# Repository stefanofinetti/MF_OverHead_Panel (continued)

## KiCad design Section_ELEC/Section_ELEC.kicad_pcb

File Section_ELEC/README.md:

# ELEC section board (v2)

The v2 board under the ELEC panel. It carries the panel's switches, annunciator LEDs and backlight, at their v1 positions, and reaches the mainboard through one ribbon and one pair of backlight wires. There are no ICs on it. The design rules shared by the eight section boards are in [`docs/board-split.md`](../docs/board-split.md).

* **PCB:** 177.5 × 39.5 mm, 2 layers, 1.6 mm. Every v1 hole is kept.
* **Status:** routed with Freerouting. ERC, DRC and schematic parity are clean. Not yet ordered.

**Top**, the panel side:

**Bottom**, with the connectors:

Rendered by KiCad from the board file. The bottom is seen from below, so it is mirrored against the top.

## Connectors

Both are new on v2 and sit on the **back**, so nothing new stands proud of the front.

| Ref | What | Goes to |
|---|---|---|
| J1 | Shrouded IDC header, 20 pins, SMD | J703 on the mainboard, straight ribbon, pin 1 to pin 1 |
| J2 | JST PH, 2 pins, SMD. Pin 1 `+9V_BL` (`+`), pin 2 the switched return (`−`) | screw terminal J603 on the mainboard |

J1 and J2 are on the back, top edge, left end.

The signal on every ribbon pin is in the design document: [ELEC — 20 pins](../docs/board-split.md#elec--20-pins).

## Switches

| Ref | Switch | Type | v1 ref |
|---|---|---|---|
| SW1 | ELEC OXY CREW SUPPLY | Korry | SW14 |
| SW2 | ELEC BATT 1 | Korry | SW15 |
| SW3 | ELEC BATT 2 | Korry | SW16 |

## Annunciators

Anodes on `+5V_LED` from the ribbon, cathodes back down the ribbon to their TLC5927 output. No resistors: the TLC5927 sets the current.

| Ref | Colour | Legend | Chain bit | Driver | v1 ref |
|---|---|---|---|---|---|
| D1 | white | `OXY_CREW_SUPPLY_OFF` | `ANN_LOWER` 4 | U501 (v1 U6) | D103 |
| D2 | amber | `ELEC_BATT_1_FAULT` | `ANN_UPPER` 14 | U503 (v1 U8) | D1 |
| D3 | white | `ELEC_BATT_1_OFF` | `ANN_LOWER` 15 | U501 (v1 U6) | D106 |
| D4 | amber | `ELEC_BATT_2_FAULT` | `ANN_UPPER` 13 | U503 (v1 U8) | D3 |
| D5 | white | `ELEC_BATT_2_OFF` | `ANN_LOWER` 14 | U501 (v1 U6) | D107 |

## Backlight

10 LEDs, 1206 (D6–D15), on 9 V, in 5 strings of two with 150 Ω (R1–R5). Each string runs at about 17 mA. `K` marks every cathode on the silkscreen.

## Assembly notes

* J3 is the BATT 1 OLED socket (PCA9548A channel 0) and J4 the BATT 2 one (channel 1), where they were on v1: 1 GND, 2 +3V3, 3 SCL, 4 SDA.
* R5 is new, 150 Ω on the back. It replaces v1 R57, which sat across the seam on the AIR COND side.
* Every part has its value, polarity or pin 1 on the silkscreen of its own side. Each part's description in the schematic names its v1 reference.

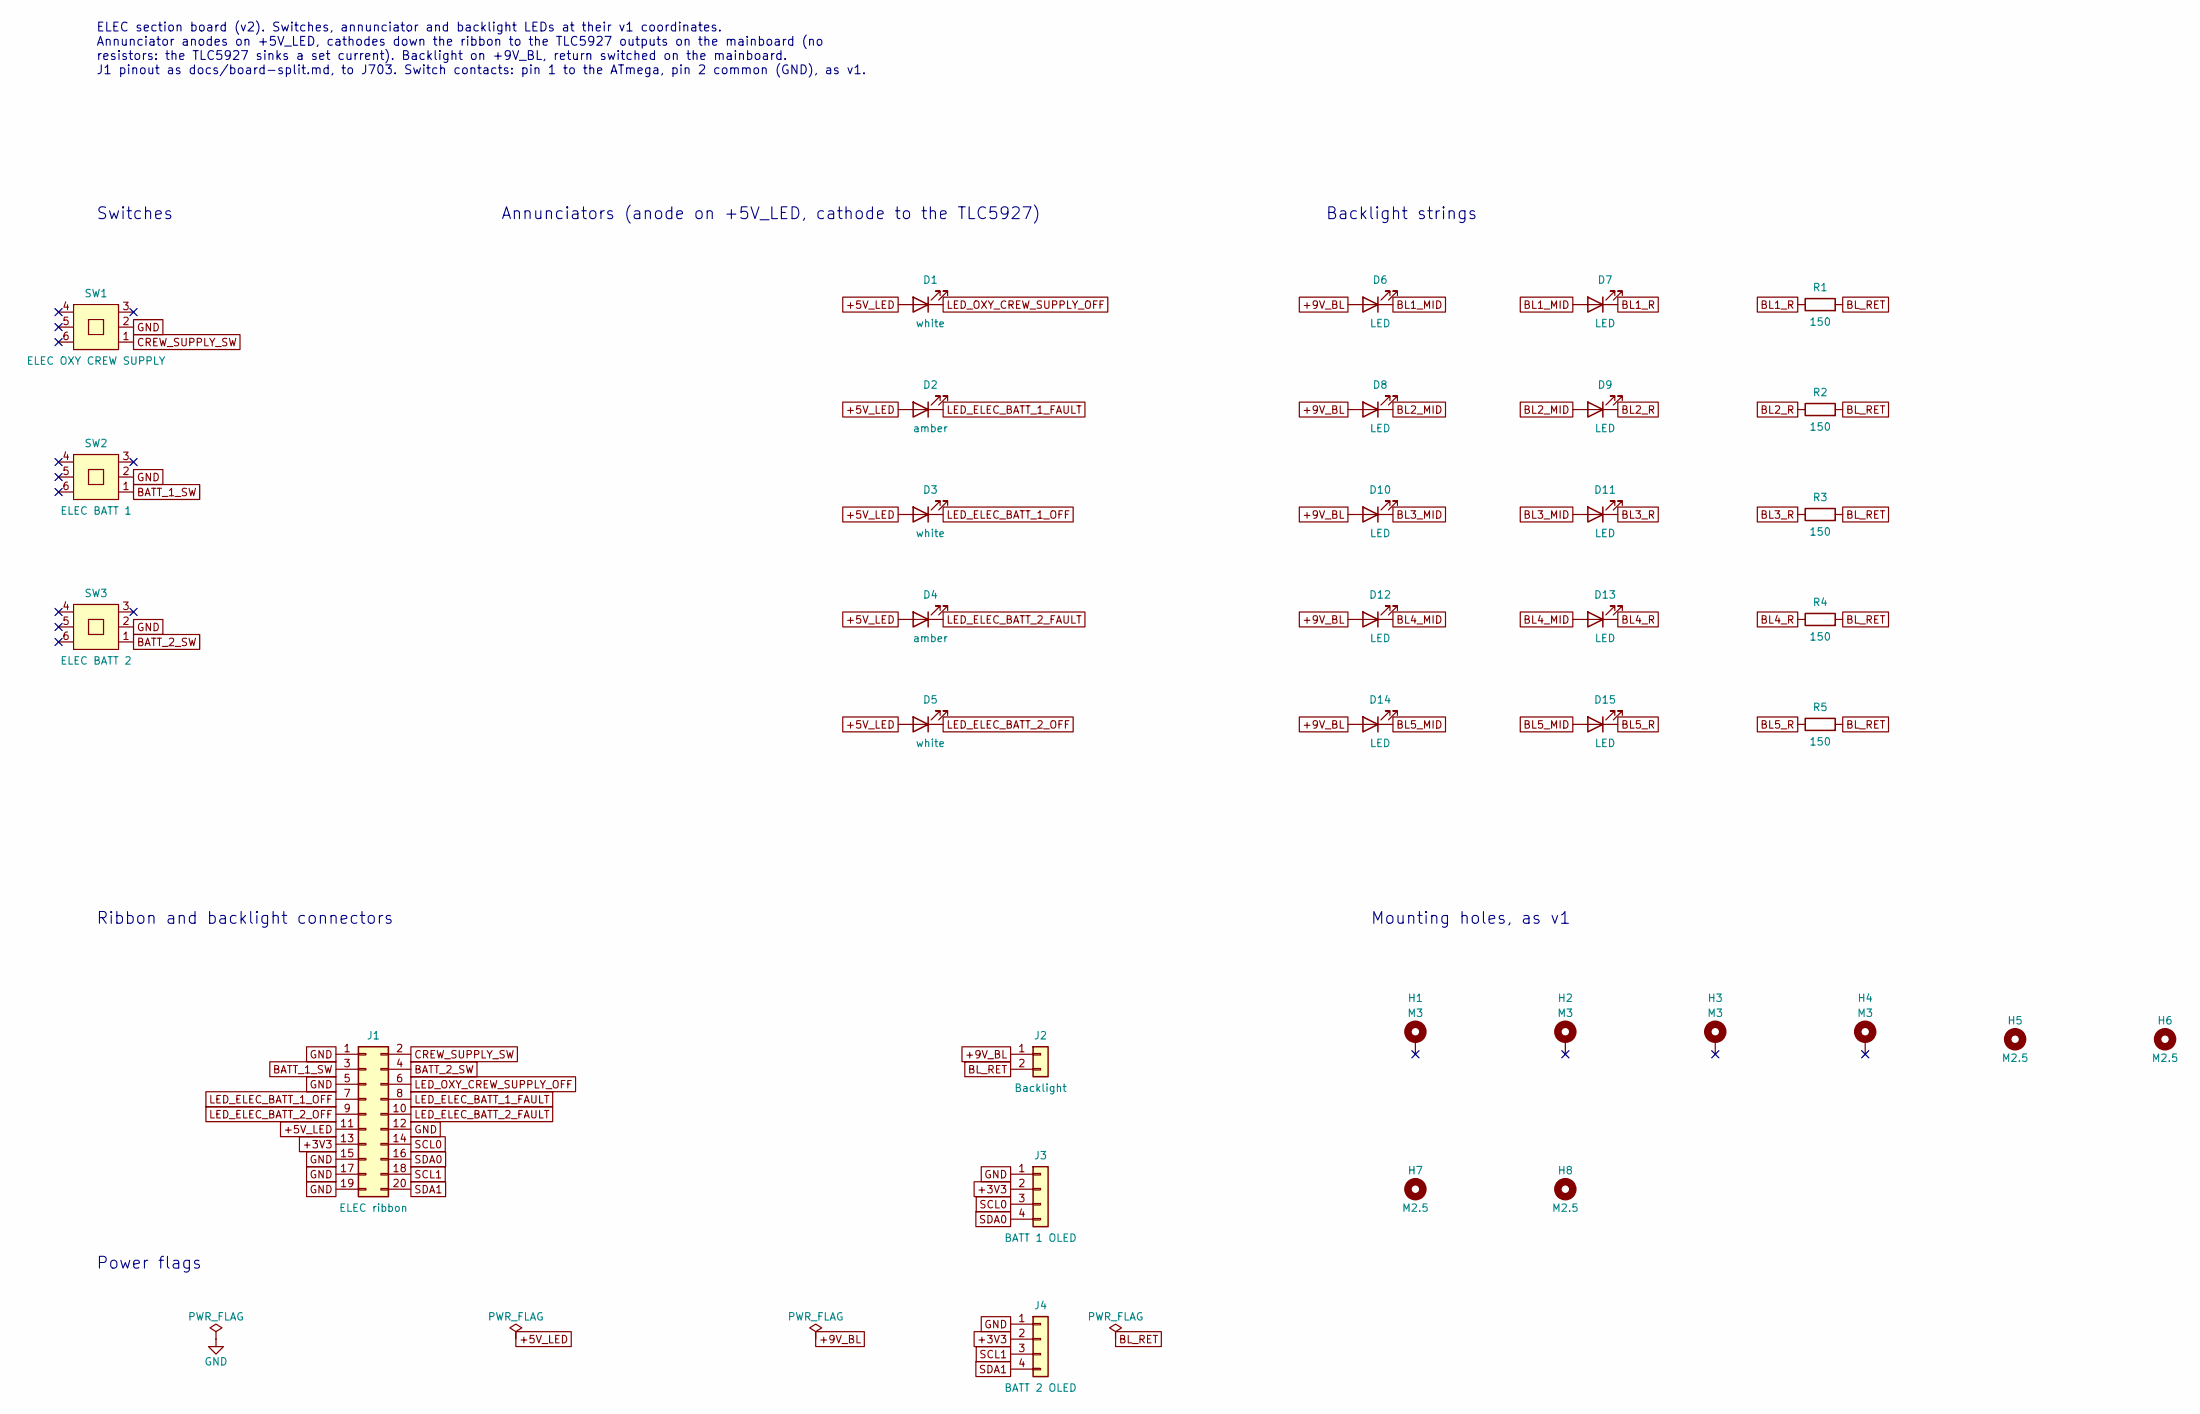
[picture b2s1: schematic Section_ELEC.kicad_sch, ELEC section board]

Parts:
D1, D3, D5: white; LED_Rectangular_W3.9mm_H1.8mm_FlatTop
D2, D4: amber; LED_Rectangular_W3.9mm_H1.8mm_FlatTop
D6, D7, D8, D9, D10, D11, D12, D13, D14, D15: LED; LED_1206_3216Metric_Pad1.42x1.75mm_HandSolder
H1, H2, H3, H4: M3; MountingHole_3.2mm_M3_DIN965_Pad_TopBottom
H5, H6, H7, H8: M2.5; MountingHole_2.7mm_M2.5
J1: ELEC ribbon; IDC-Header_2x10_P2.54mm_Vertical_SMD
J2: Backlight; JST_PH_B2B-PH-SM4-TB_1x02-1MP_P2.00mm_Vertical
J3: BATT 1 OLED; PinSocket_1x04_P2.54mm_Vertical
J4: BATT 2 OLED; PinSocket_1x04_P2.54mm_Vertical
R1, R2, R3, R4, R5: 150; R_1206_3216Metric_Pad1.30x1.75mm_HandSolder
SW1: ELEC OXY CREW SUPPLY; G-Switch_PS-7054DVB-6PN
SW2: ELEC BATT 1; G-Switch_PS-7054DVB-6PN
SW3: ELEC BATT 2; G-Switch_PS-7054DVB-6PN

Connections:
+3V3: J1.13, J3.2, J4.2
+5V_LED: D1.2 (A), D2.2 (A), D3.2 (A), D4.2 (A), D5.2 (A), J1.11
+9V_BL: D6.2 (A), D8.2 (A), D10.2 (A), D12.2 (A), D14.2 (A), J2.1
BATT_1_SW: J1.3, SW2.1
BATT_2_SW: J1.4, SW3.1
BL1_MID: D6.1 (K), D7.2 (A)
BL1_R: D7.1 (K), R1.1
BL2_MID: D8.1 (K), D9.2 (A)
BL2_R: D9.1 (K), R2.1
BL3_MID: D10.1 (K), D11.2 (A)
BL3_R: D11.1 (K), R3.1
BL4_MID: D12.1 (K), D13.2 (A)
BL4_R: D13.1 (K), R4.1
BL5_MID: D14.1 (K), D15.2 (A)
BL5_R: D15.1 (K), R5.1
BL_RET: J2.2, R1.2, R2.2, R3.2, R4.2, R5.2
CREW_SUPPLY_SW: J1.2, SW1.1
GND: J1.1, J1.5, J1.12, J1.15, J1.17, J1.19, J3.1, J4.1, SW1.2, SW2.2, SW3.2
LED_ELEC_BATT_1_FAULT: D2.1 (K), J1.8
LED_ELEC_BATT_1_OFF: D3.1 (K), J1.7
LED_ELEC_BATT_2_FAULT: D4.1 (K), J1.10
LED_ELEC_BATT_2_OFF: D5.1 (K), J1.9
LED_OXY_CREW_SUPPLY_OFF: D1.1 (K), J1.6
SCL0: J1.14, J3.3
SCL1: J1.18, J4.3
SDA0: J1.16, J3.4
SDA1: J1.20, J4.4

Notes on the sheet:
Backlight strings
Power flags
Ribbon and backlight connectors
Switches
Mounting holes, as v1
ELEC section board (v2). Switches, annunciator and backlight LEDs at their v1 coordinates. Annunciator anodes on +5V_LED, cathodes down the ribbon to the TLC5927 outputs on the mainboard (no resistors: the TLC5927 sinks a set current). Backlight on +9V_BL, return switched on the mainboard. J1 pinou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
Annunciators (anode on +5V_LED, cathode to the TLC5927)

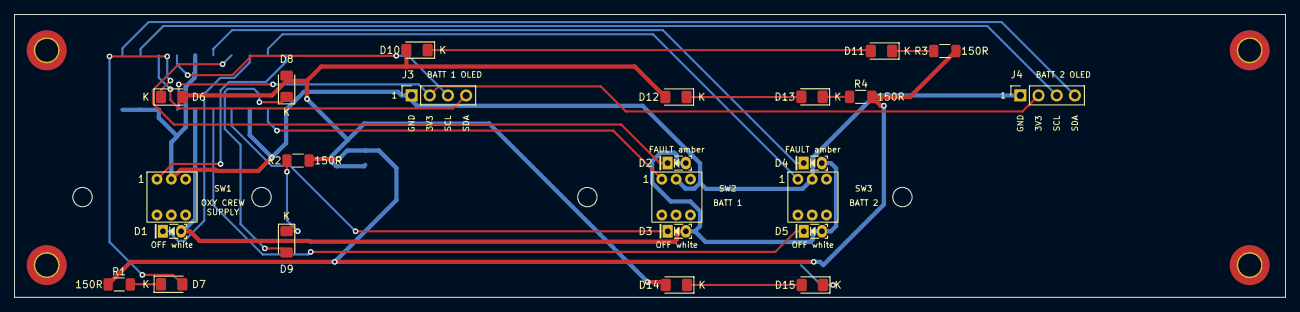
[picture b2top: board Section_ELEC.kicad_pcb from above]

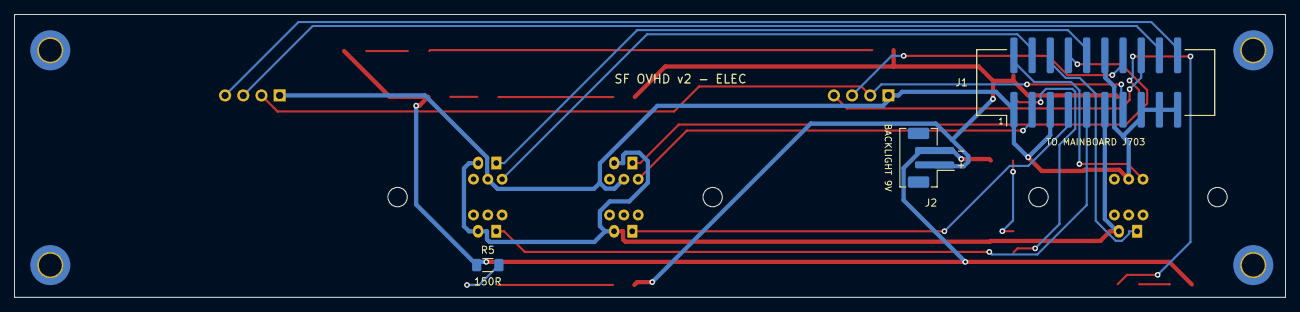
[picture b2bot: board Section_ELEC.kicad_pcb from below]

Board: 2 copper layers, 177.5 x 39.5 mm, 35 parts (3 on the bottom side), 27 nets.

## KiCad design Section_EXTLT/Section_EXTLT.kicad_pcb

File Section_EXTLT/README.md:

# EXT LT section board (v2)

The v2 board under the EXT LT panel. It carries the panel's switches, annunciator LEDs and backlight, at their v1 positions, and reaches the mainboard through one ribbon and one pair of backlight wires. There are no ICs on it. The design rules shared by the eight section boards are in [`docs/board-split.md`](../docs/board-split.md).

* **PCB:** 159.5 × 79.5 mm, 2 layers, 1.6 mm. Every v1 hole is kept.
* **Status:** routed with Freerouting. ERC, DRC and schematic parity are clean. Not yet ordered.

**Top**, the panel side:

**Bottom**, with the connectors:

Rendered by KiCad from the board file. The bottom is seen from below, so it is mirrored against the top.

## Connectors

Both are new on v2 and sit on the **back**, so nothing new stands proud of the front.

| Ref | What | Goes to |
|---|---|---|
| J1 | Shrouded IDC header, 14 pins, SMD | J706 on the mainboard, straight ribbon, pin 1 to pin 1 |
| J2 | JST PH, 2 pins, SMD. Pin 1 `+9V_BL` (`+`), pin 2 the switched return (`−`) | screw terminal J606 on the mainboard |

J1 and J2 are at the right, over the mainboard, above its TLC5927 block.

The signal on every ribbon pin is in the design document: [EXT LT — 14 pins](../docs/board-split.md#ext-lt--14-pins).

## Switches

| Ref | Switch | Type | v1 ref |
|---|---|---|---|
| SW1 | EXTLT STROBE | toggle | S7 |
| SW2 | EXTLT BEACON | toggle | S6 |
| SW3 | EXTLT WING | toggle | S5 |
| SW4 | EXTLT NAV & LOGO | toggle | S4 |
| SW5 | EXTLT RWY TURN | toggle | S8 |
| SW6 | EXTLT LDG LIGHT L | toggle | S1 |
| SW7 | EXTLT LDG LIGHT R | toggle | S2 |
| SW8 | EXTLT NOSE LIGHT | toggle | S3 |

## Backlight

31 LEDs, 1206 (D1–D31), on 9 V: 15 strings of two with 150 Ω, and one single LED with R16, 330 Ω. Each string runs at about 17 mA. `K` marks every cathode on the silkscreen.

## Assembly notes

* No annunciators, so the ribbon carries no `+5V_LED`.
* Toggles: ON-OFF-ON for LDG LIGHT L, LDG LIGHT R, NOSE LIGHT and NAV & LOGO, read on both contacts (1 and 3); ON-OFF for STROBE, BEACON, WING and RWY TURN, read on contact 1. Lever up closes contact 1, the lower pin. They are generic three-terminal PCB-pin lever toggles from AliExpress, fitted by hand. The footprint is the v1 one, whose name still carries the E-Switch number 100SP1T1B4M2QE: that is not the part fitted, and the schematic gives the toggles no part number.
* D31 is a single-LED string: on v1 it was paired with D139, now on GPWS. R16, 330 Ω on the back, gives it the same 17 mA as a pair on 150 Ω.
* Every part has its value, polarity or pin 1 on the silkscreen of its own side. Each part's description in the schematic names its v1 reference.

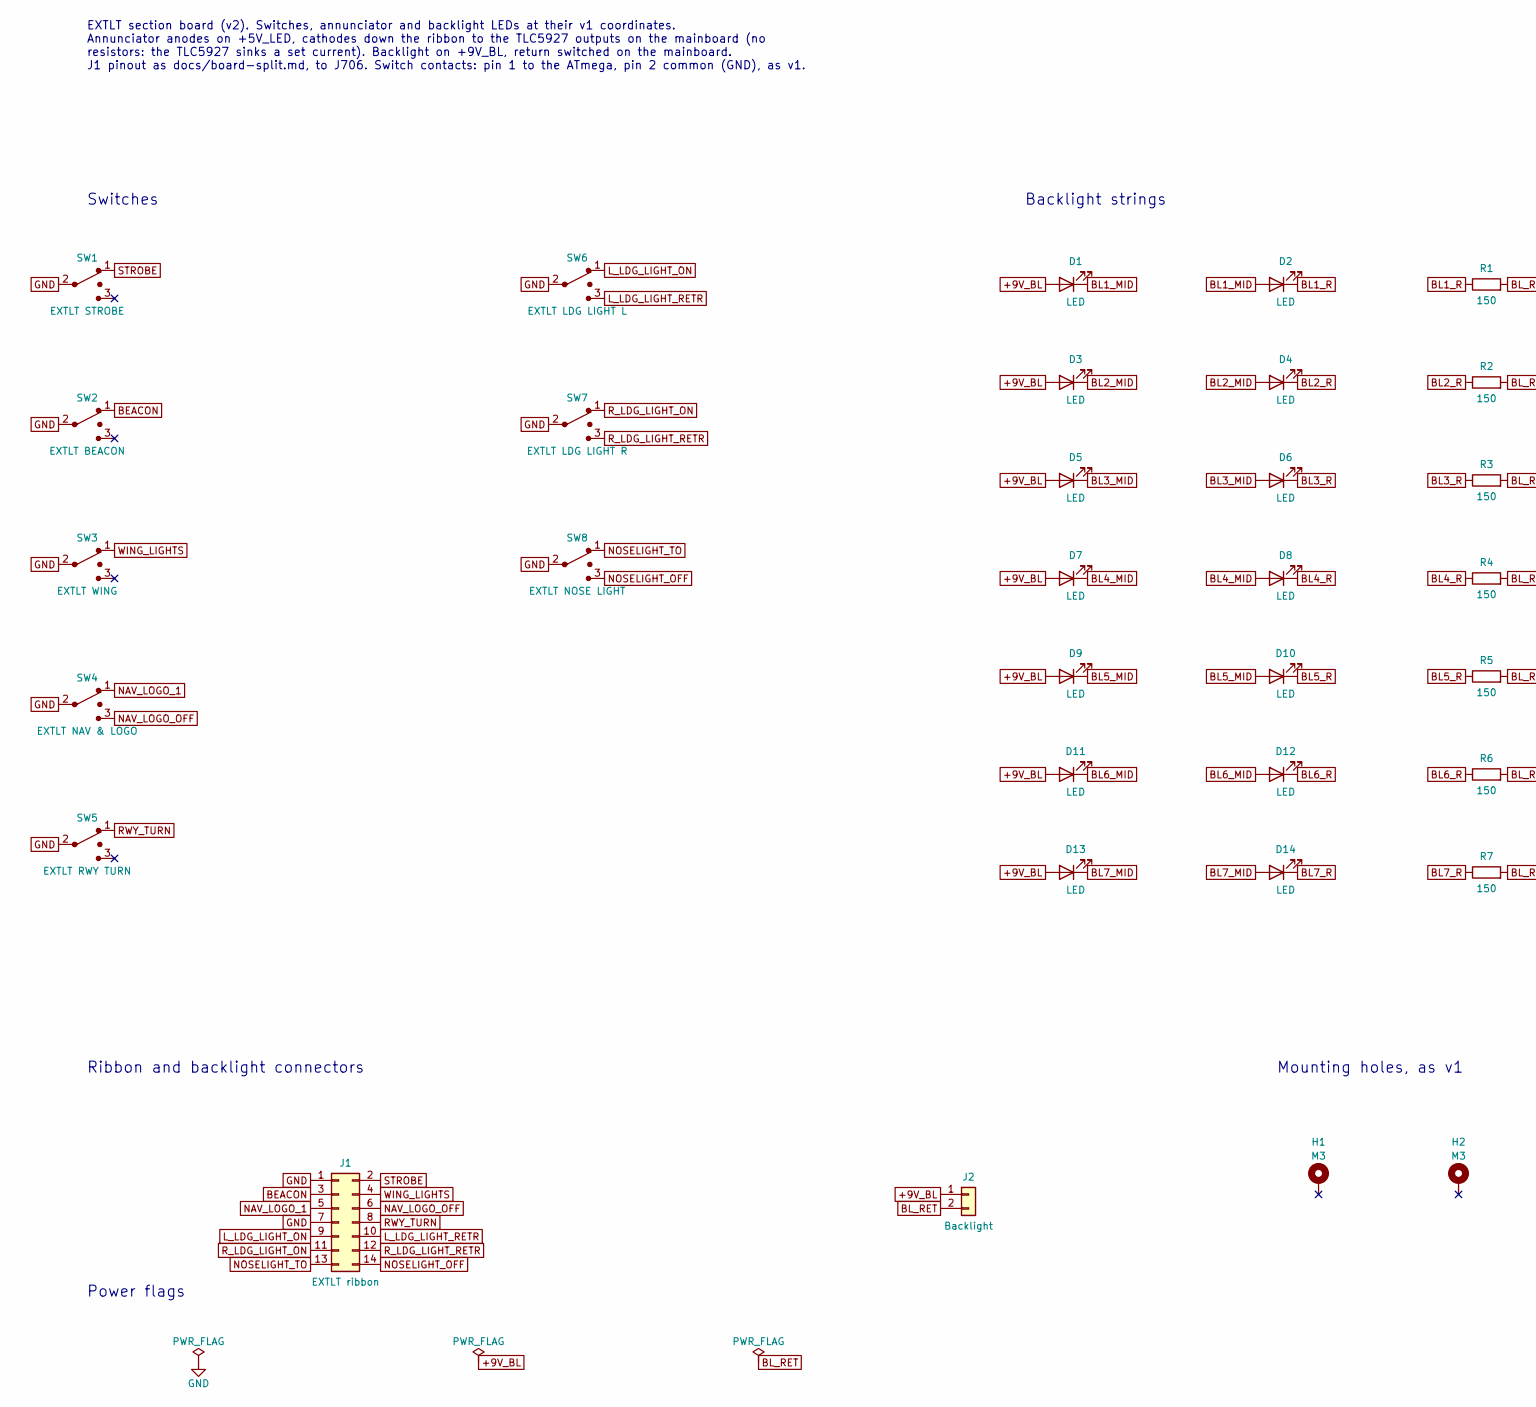
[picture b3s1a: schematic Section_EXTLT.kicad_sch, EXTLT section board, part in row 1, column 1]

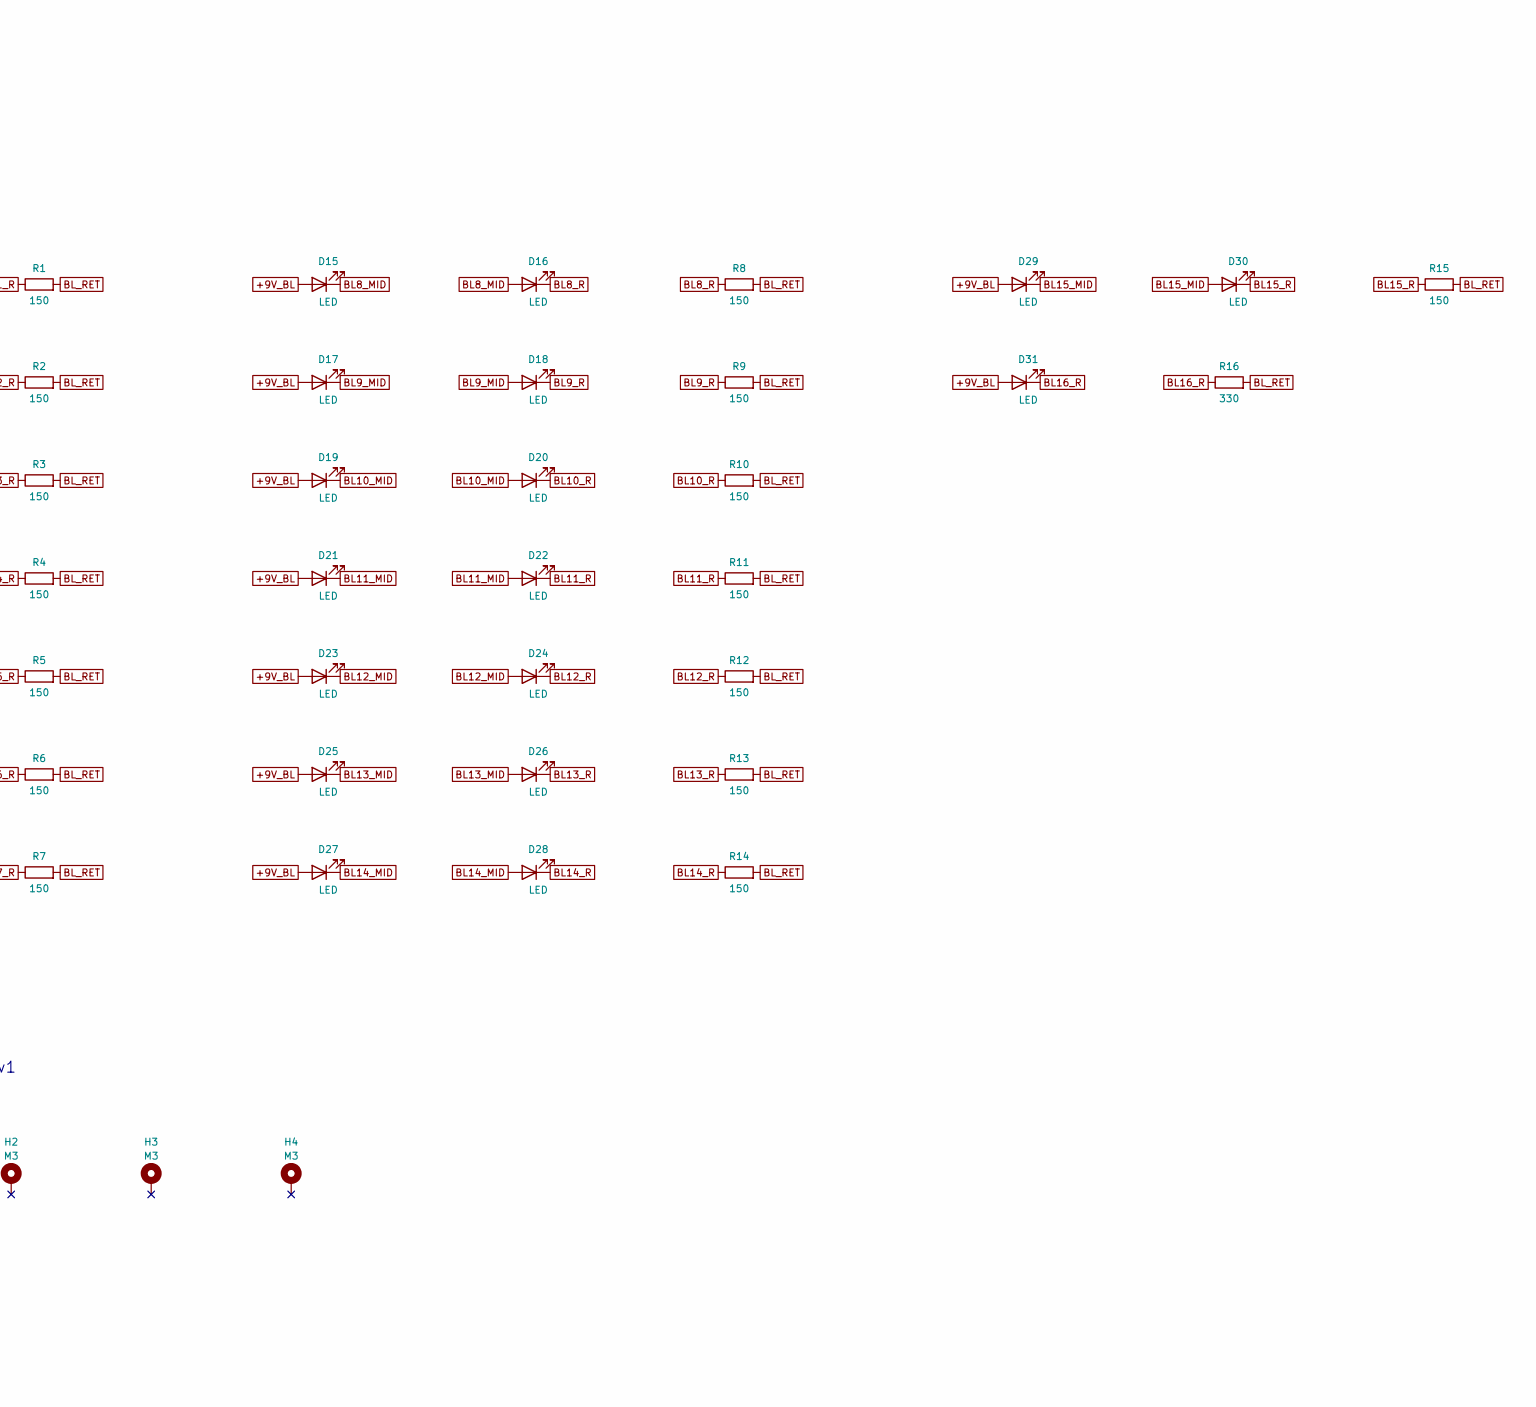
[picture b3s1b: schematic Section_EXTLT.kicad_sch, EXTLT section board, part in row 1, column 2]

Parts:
D1, D2, D3, D4, D5, D6, D7, D8, D9, D10, D11, D12, D13, D14, D15, D16, D17, D18, D19, D20, D21, D22, D23, D24, D25, D26, D27, D28, D29, D30, D31: LED; LED_1206_3216Metric_Pad1.42x1.75mm_HandSolder
H1, H2, H3, H4: M3; MountingHole_3.2mm_M3_DIN965_Pad_TopBottom
J1: EXTLT ribbon; IDC-Header_2x07_P2.54mm_Vertical_SMD
J2: Backlight; JST_PH_B2B-PH-SM4-TB_1x02-1MP_P2.00mm_Vertical
R1, R2, R3, R4, R5, R6, R7, R8, R9, R10, R11, R12, R13, R14, R15: 150; R_1206_3216Metric_Pad1.30x1.75mm_HandSolder
R16: 330; R_1206_3216Metric_Pad1.30x1.75mm_HandSolder
SW1: EXTLT STROBE; Toggle_Switch_100SP1T1B4M2QE
SW2: EXTLT BEACON; Toggle_Switch_100SP1T1B4M2QE
SW3: EXTLT WING; Toggle_Switch_100SP1T1B4M2QE
SW4: EXTLT NAV & LOGO; Toggle_Switch_100SP1T1B4M2QE
SW5: EXTLT RWY TURN; Toggle_Switch_100SP1T1B4M2QE
SW6: EXTLT LDG LIGHT L; Toggle_Switch_100SP1T1B4M2QE
SW7: EXTLT LDG LIGHT R; Toggle_Switch_100SP1T1B4M2QE
SW8: EXTLT NOSE LIGHT; Toggle_Switch_100SP1T1B4M2QE

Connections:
+9V_BL: D1.2 (A), D3.2 (A), D5.2 (A), D7.2 (A), D9.2 (A), D11.2 (A), D13.2 (A), D15.2 (A), D17.2 (A), D19.2 (A), D21.2 (A), D23.2 (A), D25.2 (A), D27.2 (A), D29.2 (A), D31.2 (A), J2.1
BEACON: J1.3, SW2.1
BL1_MID: D1.1 (K), D2.2 (A)
BL1_R: D2.1 (K), R1.1
BL2_MID: D3.1 (K), D4.2 (A)
BL2_R: D4.1 (K), R2.1
BL3_MID: D5.1 (K), D6.2 (A)
BL3_R: D6.1 (K), R3.1
BL4_MID: D7.1 (K), D8.2 (A)
BL4_R: D8.1 (K), R4.1
BL5_MID: D9.1 (K), D10.2 (A)
BL5_R: D10.1 (K), R5.1
BL6_MID: D11.1 (K), D12.2 (A)
BL6_R: D12.1 (K), R6.1
BL7_MID: D13.1 (K), D14.2 (A)
BL7_R: D14.1 (K), R7.1
BL8_MID: D15.1 (K), D16.2 (A)
BL8_R: D16.1 (K), R8.1
BL9_MID: D17.1 (K), D18.2 (A)
BL9_R: D18.1 (K), R9.1
BL10_MID: D19.1 (K), D20.2 (A)
BL10_R: D20.1 (K), R10.1
BL11_MID: D21.1 (K), D22.2 (A)
BL11_R: D22.1 (K), R11.1
BL12_MID: D23.1 (K), D24.2 (A)
BL12_R: D24.1 (K), R12.1
BL13_MID: D25.1 (K), D26.2 (A)
BL13_R: D26.1 (K), R13.1
BL14_MID: D27.1 (K), D28.2 (A)
BL14_R: D28.1 (K), R14.1
BL15_MID: D29.1 (K), D30.2 (A)
BL15_R: D30.1 (K), R15.1
BL16_R: D31.1 (K), R16.1
BL_RET: J2.2, R1.2, R2.2, R3.2, R4.2, R5.2, R6.2, R7.2, R8.2, R9.2, R10.2, R11.2, R12.2, R13.2, R14.2, R15.2, R16.2
GND: J1.1, J1.7, SW1.2 (Com), SW2.2 (Com), SW3.2 (Com), SW4.2 (Com), SW5.2 (Com), SW6.2 (Com), SW7.2 (Com), SW8.2 (Com)
L_LDG_LIGHT_ON: J1.9, SW6.1
L_LDG_LIGHT_RETR: J1.10, SW6.3
NAV_LOGO_1: J1.5, SW4.1
NAV_LOGO_OFF: J1.6, SW4.3
NOSELIGHT_OFF: J1.14, SW8.3
NOSELIGHT_TO: J1.13, SW8.1
RWY_TURN: J1.8, SW5.1
R_LDG_LIGHT_ON: J1.11, SW7.1
R_LDG_LIGHT_RETR: J1.12, SW7.3
STROBE: J1.2, SW1.1
WING_LIGHTS: J1.4, SW3.1

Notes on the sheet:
Power flags
Ribbon and backlight connectors
Mounting holes, as v1
Switches
Backlight strings
EXTLT section board (v2). Switches, annunciator and backlight LEDs at their v1 coordinates. Annunciator anodes on +5V_LED, cathodes down the ribbon to the TLC5927 outputs on the mainboard (no resistors: the TLC5927 sinks a set current). Backlight on +9V_BL, return switched on the mainboard. J1 pino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

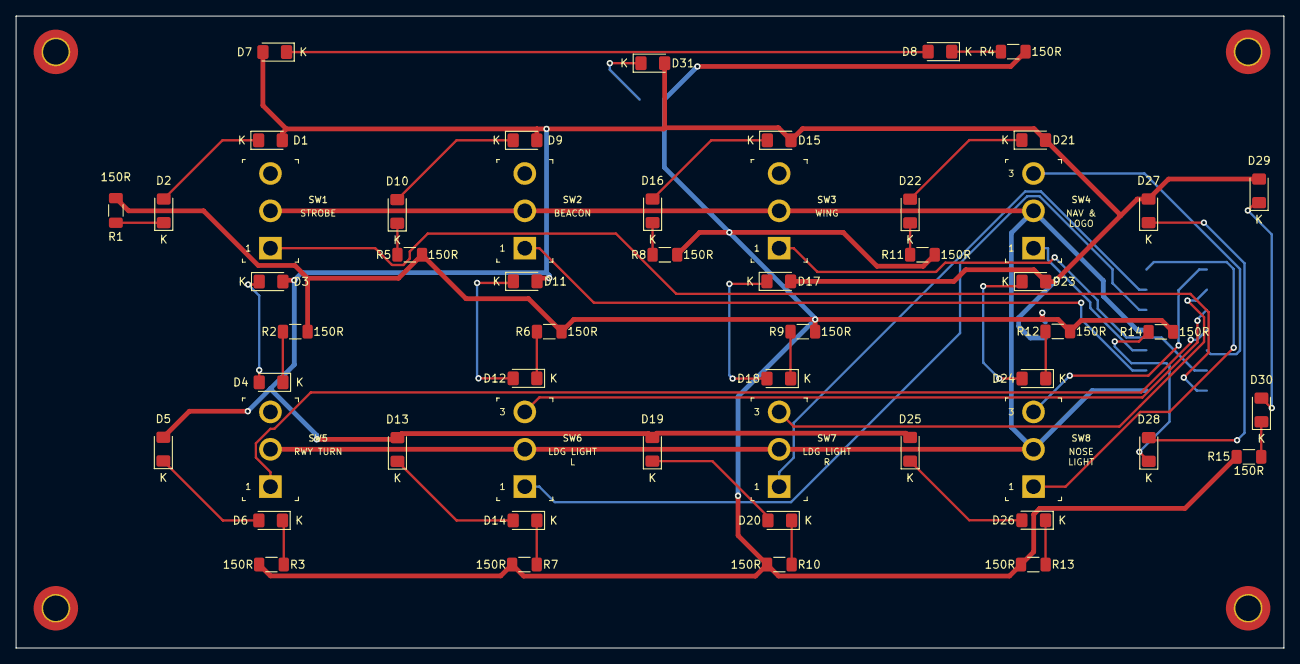
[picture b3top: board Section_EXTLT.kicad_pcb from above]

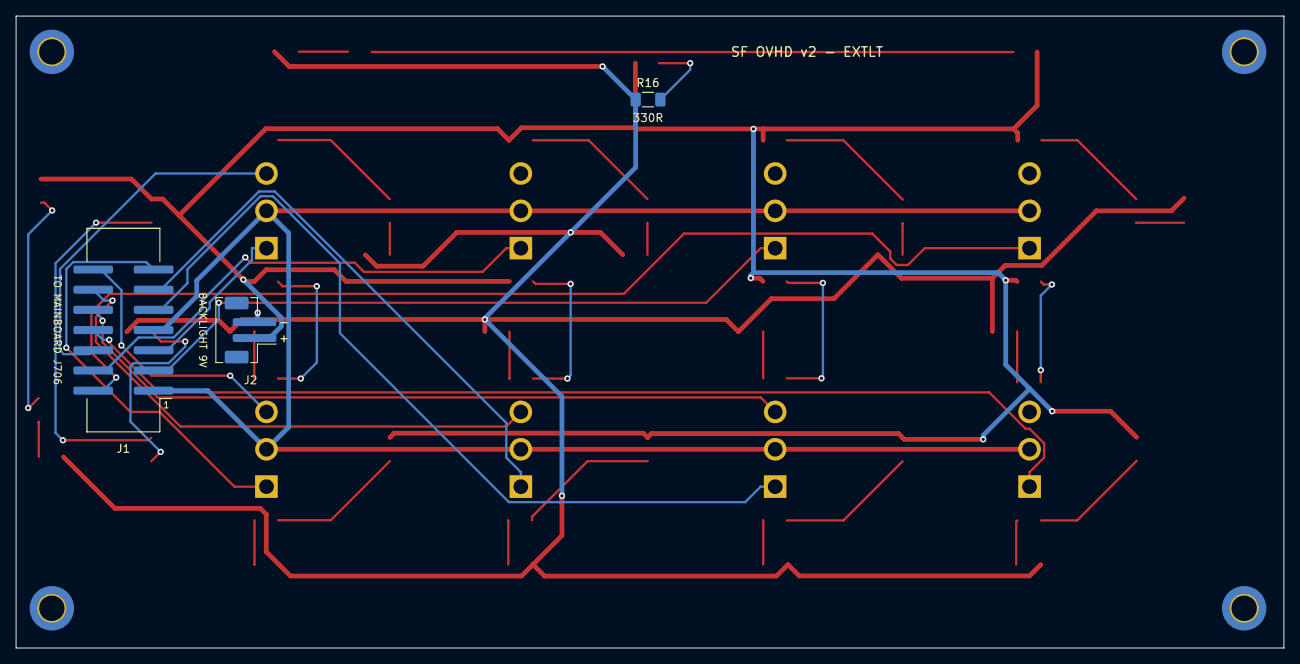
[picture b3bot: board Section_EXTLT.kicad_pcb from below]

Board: 2 copper layers, 159.5 x 79.5 mm, 61 parts (3 on the bottom side), 46 nets.

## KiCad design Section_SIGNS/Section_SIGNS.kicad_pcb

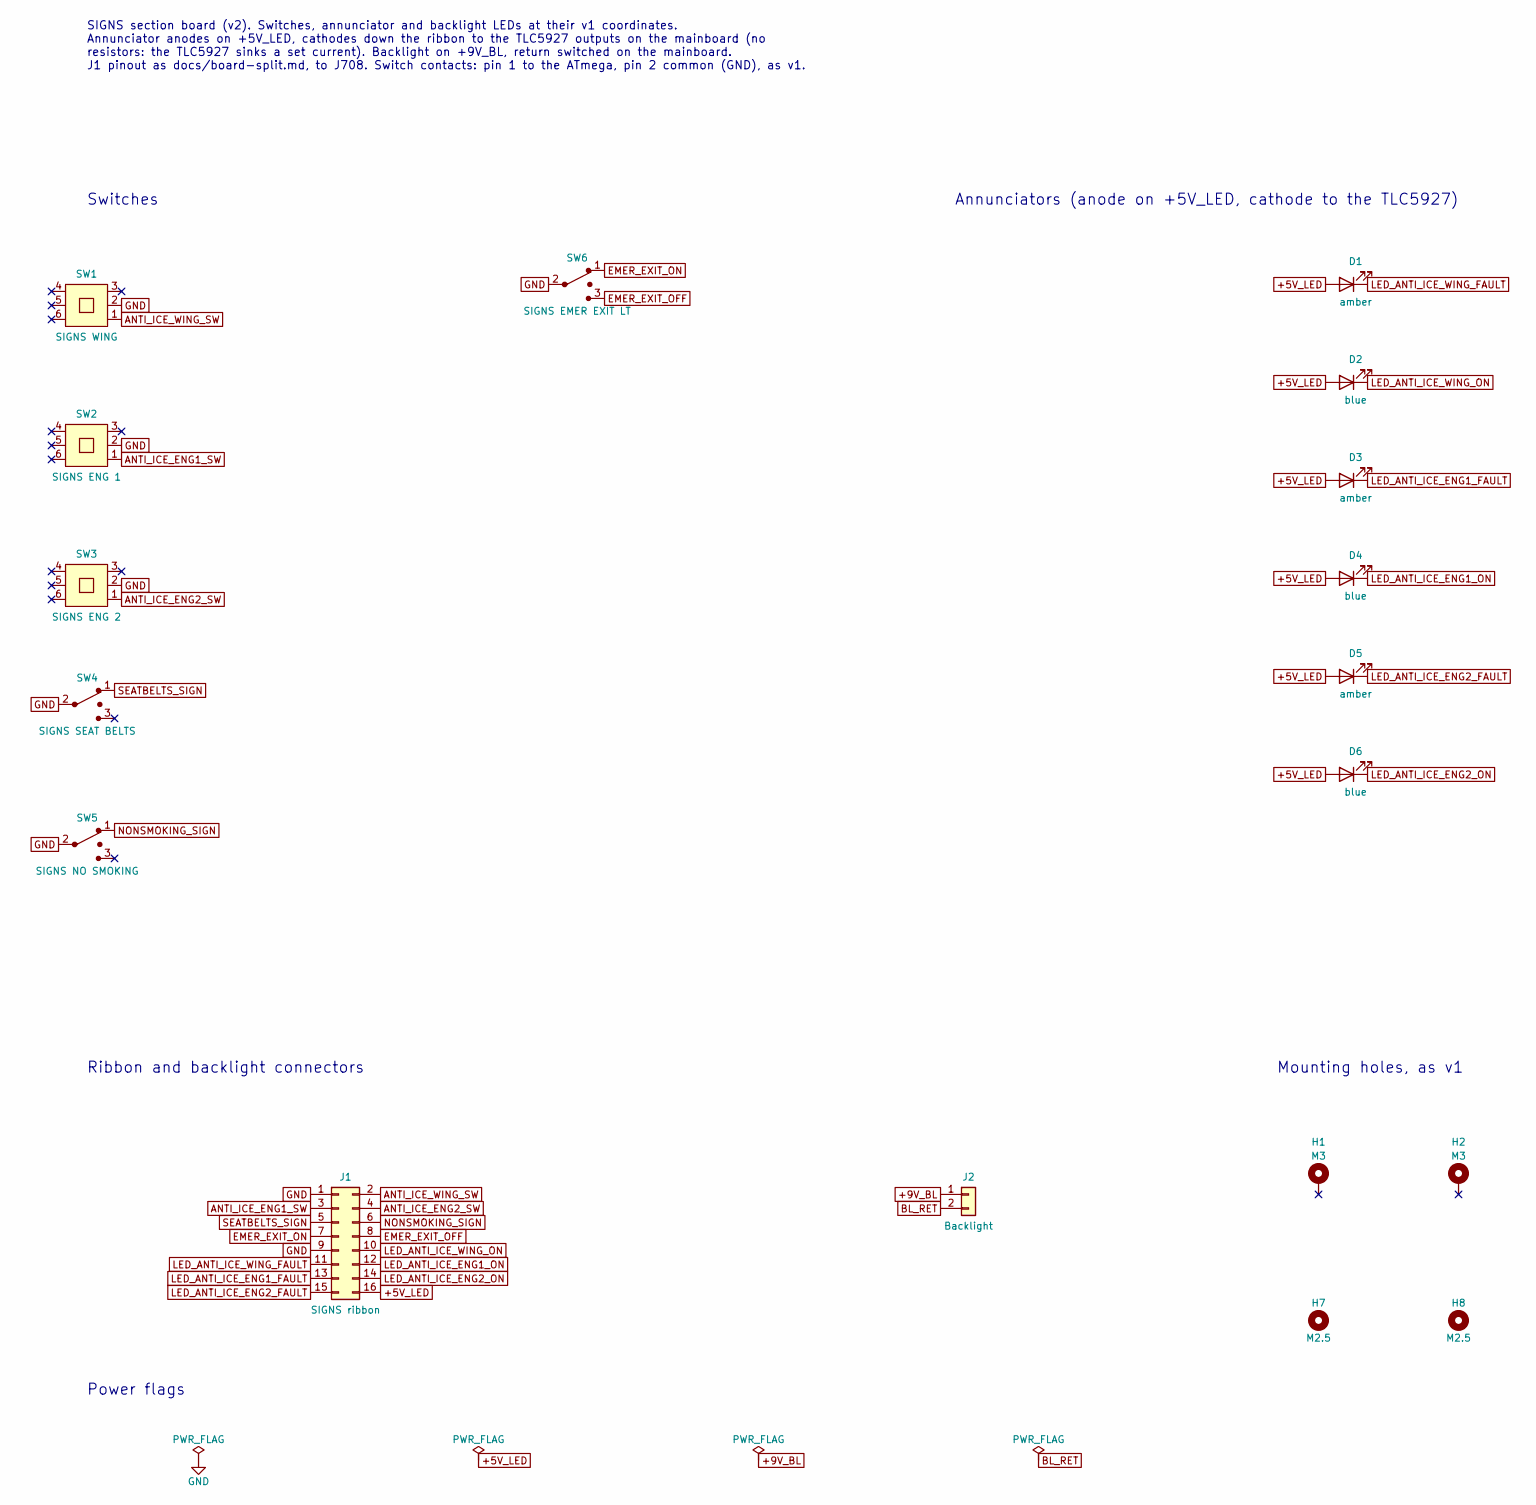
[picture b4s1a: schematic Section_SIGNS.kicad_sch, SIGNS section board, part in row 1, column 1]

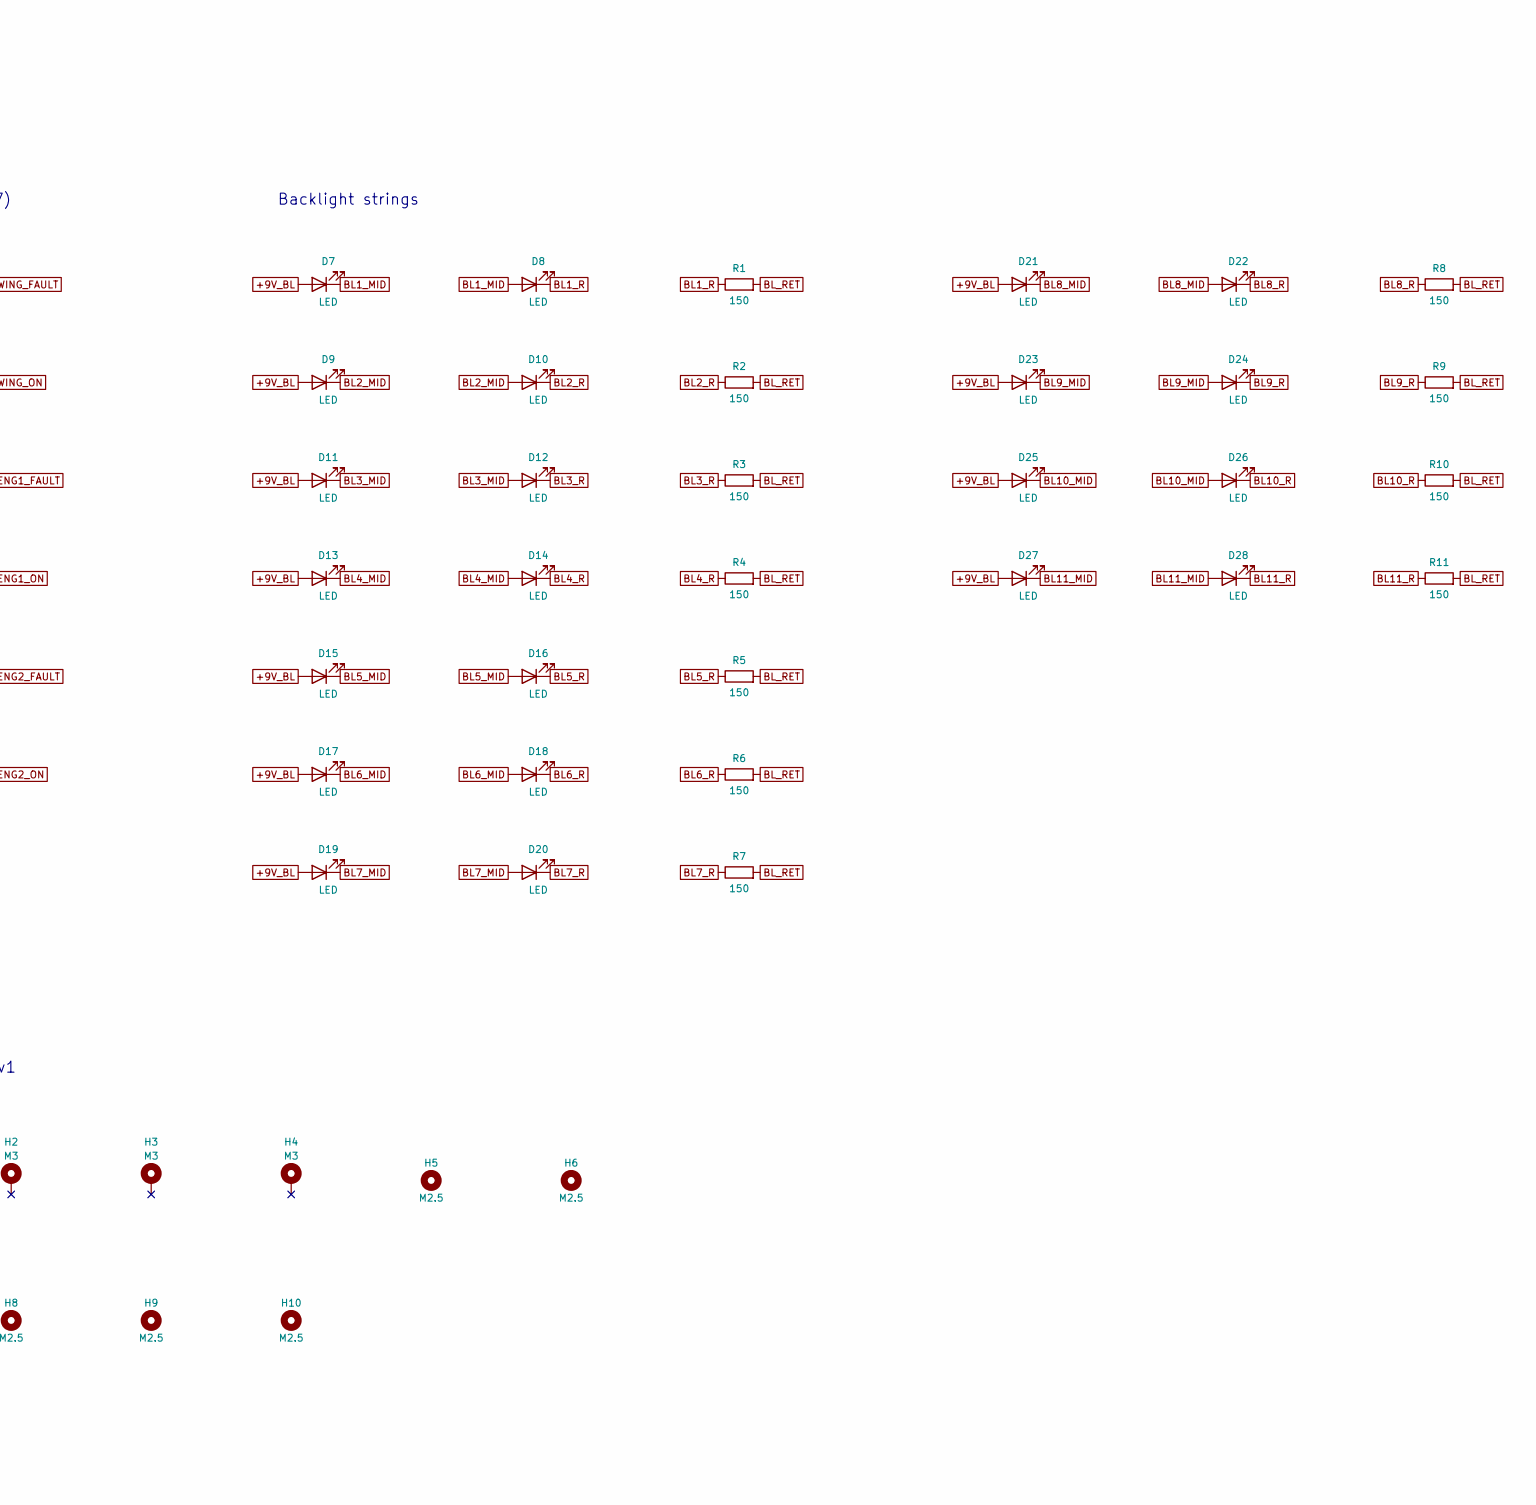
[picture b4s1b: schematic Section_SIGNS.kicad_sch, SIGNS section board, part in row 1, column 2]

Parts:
D1, D3, D5: amber; LED_Rectangular_W3.9mm_H1.8mm_FlatTop
D2, D4, D6: blue; LED_Rectangular_W3.9mm_H1.8mm_FlatTop
D7, D8, D9, D10, D11, D12, D13, D14, D15, D16, D17, D18, D19, D20, D21, D22, D23, D24, D25, D26, D27, D28: LED; LED_1206_3216Metric_Pad1.42x1.75mm_HandSolder
H1, H2, H3, H4: M3; MountingHole_3.2mm_M3_DIN965_Pad_TopBottom
H5, H6, H7, H8, H9, H10: M2.5; MountingHole_2.7mm_M2.5
J1: SIGNS ribbon; IDC-Header_2x08_P2.54mm_Vertical_SMD
J2: Backlight; JST_PH_B2B-PH-SM4-TB_1x02-1MP_P2.00mm_Vertical
R1, R2, R3, R4, R5, R6, R7, R8, R9, R10, R11: 150; R_1206_3216Metric_Pad1.30x1.75mm_HandSolder
SW1: SIGNS WING; G-Switch_PS-7054DVB-6PN
SW2: SIGNS ENG 1; G-Switch_PS-7054DVB-6PN
SW3: SIGNS ENG 2; G-Switch_PS-7054DVB-6PN
SW4: SIGNS SEAT BELTS; Toggle_Switch_100SP1T1B4M2QE
SW5: SIGNS NO SMOKING; Toggle_Switch_100SP1T1B4M2QE
SW6: SIGNS EMER EXIT LT; Toggle_Switch_100SP1T1B4M2QE

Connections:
+5V_LED: D1.2 (A), D2.2 (A), D3.2 (A), D4.2 (A), D5.2 (A), D6.2 (A), J1.16
+9V_BL: D7.2 (A), D9.2 (A), D11.2 (A), D13.2 (A), D15.2 (A), D17.2 (A), D19.2 (A), D21.2 (A), D23.2 (A), D25.2 (A), D27.2 (A), J2.1
ANTI_ICE_ENG1_SW: J1.3, SW2.1
ANTI_ICE_ENG2_SW: J1.4, SW3.1
ANTI_ICE_WING_SW: J1.2, SW1.1
BL1_MID: D7.1 (K), D8.2 (A)
BL1_R: D8.1 (K), R1.1
BL2_MID: D9.1 (K), D10.2 (A)
BL2_R: D10.1 (K), R2.1
BL3_MID: D11.1 (K), D12.2 (A)
BL3_R: D12.1 (K), R3.1
BL4_MID: D13.1 (K), D14.2 (A)
BL4_R: D14.1 (K), R4.1
BL5_MID: D15.1 (K), D16.2 (A)
BL5_R: D16.1 (K), R5.1
BL6_MID: D17.1 (K), D18.2 (A)
BL6_R: D18.1 (K), R6.1
BL7_MID: D19.1 (K), D20.2 (A)
BL7_R: D20.1 (K), R7.1
BL8_MID: D21.1 (K), D22.2 (A)
BL8_R: D22.1 (K), R8.1
BL9_MID: D23.1 (K), D24.2 (A)
BL9_R: D24.1 (K), R9.1
BL10_MID: D25.1 (K), D26.2 (A)
BL10_R: D26.1 (K), R10.1
BL11_MID: D27.1 (K), D28.2 (A)
BL11_R: D28.1 (K), R11.1
BL_RET: J2.2, R1.2, R2.2, R3.2, R4.2, R5.2, R6.2, R7.2, R8.2, R9.2, R10.2, R11.2
EMER_EXIT_OFF: J1.8, SW6.3
EMER_EXIT_ON: J1.7, SW6.1
GND: J1.1, J1.9, SW1.2, SW2.2, SW3.2, SW4.2 (Com), SW5.2 (Com), SW6.2 (Com)
LED_ANTI_ICE_ENG1_FAULT: D3.1 (K), J1.13
LED_ANTI_ICE_ENG1_ON: D4.1 (K), J1.12
LED_ANTI_ICE_ENG2_FAULT: D5.1 (K), J1.15
LED_ANTI_ICE_ENG2_ON: D6.1 (K), J1.14
LED_ANTI_ICE_WING_FAULT: D1.1 (K), J1.11
LED_ANTI_ICE_WING_ON: D2.1 (K), J1.10
NONSMOKING_SIGN: J1.6, SW5.1
SEATBELTS_SIGN: J1.5, SW4.1

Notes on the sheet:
Mounting holes, as v1
Backlight strings
SIGNS section board (v2). Switches, annunciator and backlight LEDs at their v1 coordinates. Annunciator anodes on +5V_LED, cathodes down the ribbon to the TLC5927 outputs on the mainboard (no resistors: the TLC5927 sinks a set current). Backlight on +9V_BL, return switched on the mainboard. J1 pino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
Switches
Ribbon and backlight connectors
Annunciators (anode on +5V_LED, cathode to the TLC5927)
Power flags
